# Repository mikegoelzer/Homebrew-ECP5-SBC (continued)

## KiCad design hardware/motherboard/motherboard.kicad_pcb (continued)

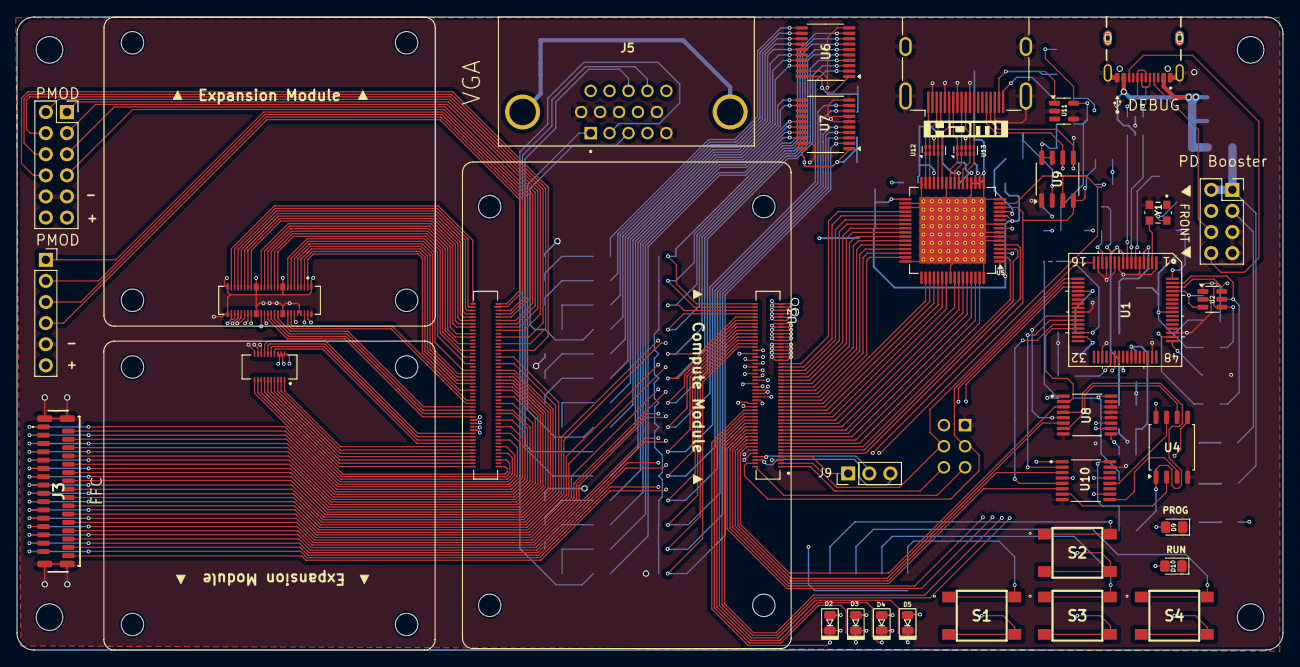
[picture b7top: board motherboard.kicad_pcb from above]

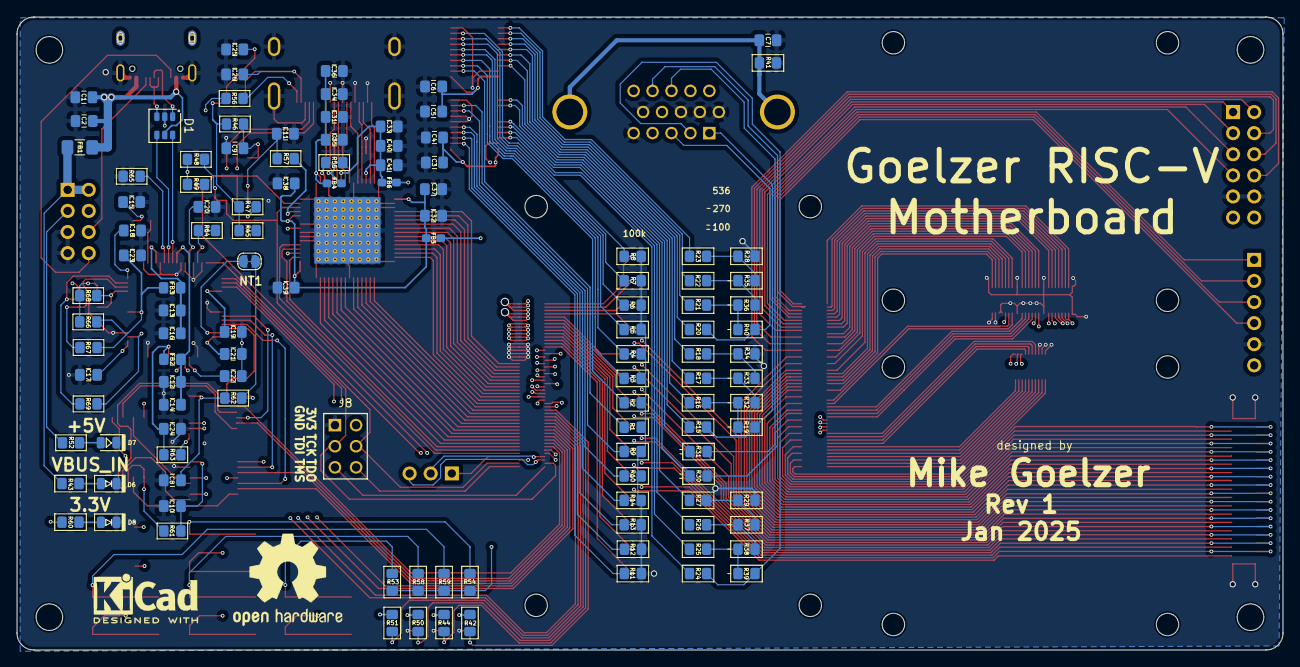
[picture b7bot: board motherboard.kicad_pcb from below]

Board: 4 copper layers, 152.4 x 76.2 mm, 160 parts (120 on the bottom side), 250 nets.

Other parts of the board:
G3: LOGO; hdmi-400x80-mil
G4: LOGO; usb-logo-100mil

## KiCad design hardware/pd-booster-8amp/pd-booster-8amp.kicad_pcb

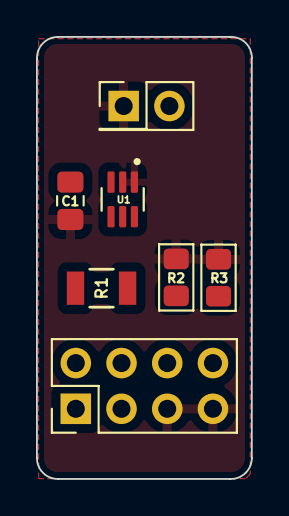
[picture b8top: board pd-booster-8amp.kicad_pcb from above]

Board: 2 copper layers, 11.9 x 24.6 mm, 7 parts (0 on the bottom side), 6 nets, no tracks yet.

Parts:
C1: 0.1uF; C_0805_2012Metric_Pad1.18x1.45mm_HandSolder
J1: 2x4 male 0.1"; PinHeader_2x04_P2.54mm_Vertical
J2: PH1RB-02-UA; PinHeader_2x01_P2.54mm_Vertical
R1: 2mΩ 1% 1W; STA_CSNL1206_STP
R2, R3: 5.1k 1%; R_0805_2012Metric_Pad1.15x1.40mm_HandSolder
U1: INA211BIDCKT; SOT65P210X110-6N

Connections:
/5V_OUT: J1.3, J1.4, R1.2, U1.5 (-IN)
/CC1: J1.6, R2.1
/CC2: J1.8, R3.1
/ISENSE: J2.2, U1.6 (OUT)
/VBUS_IN: C1.1, J1.1, J1.2, R1.1, U1.3 (V+), U1.4 (+IN)
GND: C1.2, J1.5, J1.7, J2.1, R2.2, R3.2, U1.1 (REF), U1.2 (GND)

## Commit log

2024-09-07 constraints for osh park 2-layer
2024-09-08 add led calculators
2024-09-08 fix working directory for python script debugging
2024-09-08 add script to add properties to .kicad_sym files
2024-09-10 handle quoted attribute values correctly
2024-09-10 get library and part names correct even in edge cases
2024-09-10 kicad sym editor default supports usual fields
2024-09-15 efuse version - abandoned, unecessarily complex
2024-09-19 helper script for pasting e96 table into excel
2024-12-16 add pcbway bom
2024-12-17 compute module rev 1
2024-12-23 update cm notes deck with additional slides
2024-12-23 add parts
2024-12-23 df40 footprint: remove manual F.Paste rects, add F.Paste to each pad, shrink stencil aperture 15%
2024-12-23 df40 footprint: make pads rounded rects for improved paste release
2024-12-23 script used to add F.Paste layer to all pads in footprint
2024-12-23 updated script comment
2024-12-23 df40 adapter board rev 0 - final release to mfgr
2025-01-06 motherboard rev 1
2025-01-06 rename null version of current booster to pd-booster-null
2025-01-06 split out USB-PD 8A version of pd-booster
2025-01-06 kicad project renamer script
2025-01-07 note error: wrong TVS clamp used
2025-01-07 remove old psu project
2025-01-10 complete: pd-booster-16amps rev 1 + pd-booster-null
2025-01-11 motherboard: add dimensions, add note to expand ffc
2025-01-11 calcs for TPS25947 eFuse for future power supply
2025-01-11 update slides with info on hat
2025-01-11 fix bug that was processing .kicad_sch file twice
2025-01-11 Make mousebites library project-specific version
2025-01-15 hat v1
2025-01-15 add hat v1 notes
2025-01-15 hat: move sdcard to edge
2025-01-15 hat zone fill
2025-01-15 hat rev 1 shortened pcb - release to manufacturing
2025-01-15 hat: revert to full size pcb, rev 1 final (7fcdf54b)
2025-01-26 (no changes)
2025-01-31 reduce stencil aperture shrink to max 2.5%
2025-02-02 generate pd-16amps bom
2025-02-02 additional parts purchase
2025-02-02 bom excel sheet spacing
2025-02-02 recenter pcb for printing
2025-02-07 reflect addl order of forgotten motherboard parts
2025-02-07 correct some bom designators
2025-04-23 add readmes
2025-04-23 readme updates
2025-04-23 minor changes readme
2025-04-23 readme fix links
2025-04-23 add license
2025-04-23 correct license in readme
2025-04-23 readme fix
2025-04-23 readme: shorten
2025-04-23 readme
